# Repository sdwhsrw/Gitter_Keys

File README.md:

# Warning: The project is still in progress.
# The project code and design files have not yet been organized and uploaded.

# Gitter_Keys
Gitter is an open-source key matrix project. Gitter_Keys is the mechanical keys key version of it. 

Gitter is designed to easy build. 
It uses raspberry pi pico as controller, which you can easily get with 4 to 5 Euros
The smd components are easy to solder even for beginner. 

# BOM

# Building guide
to be continue

# Links

https://www.instagram.com/wqnmf2046/

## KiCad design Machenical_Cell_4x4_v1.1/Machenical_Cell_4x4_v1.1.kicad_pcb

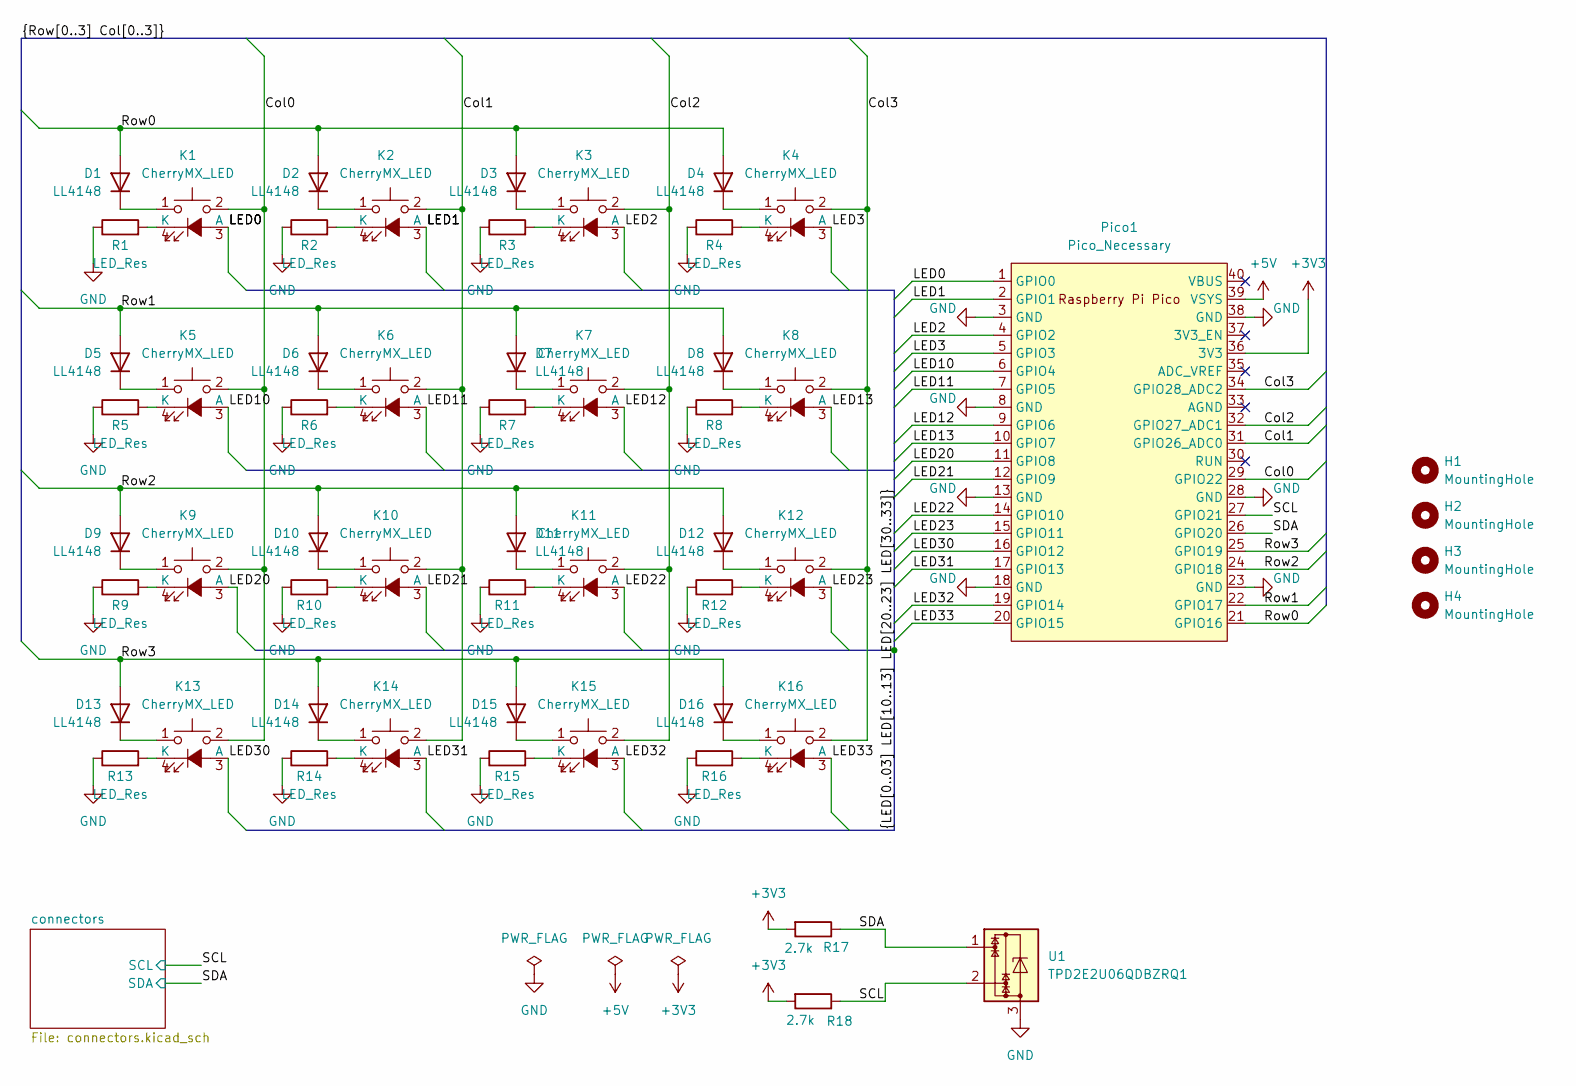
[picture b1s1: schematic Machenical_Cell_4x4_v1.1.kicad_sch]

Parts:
D1, D2, D3, D4, D5, D6, D7, D8, D9, D10, D11, D12, D13, D14, D15, D16: LL4148; D_MiniMELF
H1, H2, H3, H4: MountingHole; Moutinghole_M2.5
K1, K2, K3, K4, K5, K6, K7, K8, K9, K10, K11, K12, K13, K14, K15, K16: CherryMX_LED; MX-Hotswap-1U-1206-Reserved-LED
Pico1: Pico_Necessary; Pico_THR_Necessary
R1, R2, R3, R4, R5, R6, R7, R8, R9, R10, R11, R12, R13, R14, R15, R16: LED_Res; R_0805_2012Metric_Pad1.20x1.40mm_HandSolder
R17, R18: 2.7k; R_0805_2012Metric_Pad1.20x1.40mm_HandSolder
U1: TPD2E2U06QDBZRQ1; SOT-323_SC-70

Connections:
+3V3: Pico1.36 (3V3), R17.2, R18.2; also elsewhere on the board
+5V: Pico1.39 (VSYS); also elsewhere on the board
/Col0: K1.2, K5.2, K9.2, K13.2, Pico1.29 (GPIO22)
/Col1: K2.2, K6.2, K10.2, K14.2, Pico1.31 (GPIO26_ADC0)
/Col2: K3.2, K7.2, K11.2, K15.2, Pico1.32 (GPIO27_ADC1)
/Col3: K4.2, K8.2, K12.2, K16.2, Pico1.34 (GPIO28_ADC2)
/LED0: K1.3 (A), Pico1.1 (GPIO0)
/LED1: K2.3 (A), Pico1.2 (GPIO1)
/LED2: K3.3 (A), Pico1.4 (GPIO2)
/LED3: K4.3 (A), Pico1.5 (GPIO3)
/LED10: K5.3 (A), Pico1.6 (GPIO4)
/LED11: K6.3 (A), Pico1.7 (GPIO5)
/LED12: K7.3 (A), Pico1.9 (GPIO6)
/LED13: K8.3 (A), Pico1.10 (GPIO7)
/LED20: K9.3 (A), Pico1.11 (GPIO8)
/LED21: K10.3 (A), Pico1.12 (GPIO9)
/LED22: K11.3 (A), Pico1.14 (GPIO10)
/LED23: K12.3 (A), Pico1.15 (GPIO11)
/LED30: K13.3 (A), Pico1.16 (GPIO12)
/LED31: K14.3 (A), Pico1.17 (GPIO13)
/LED32: K15.3 (A), Pico1.19 (GPIO14)
/LED33: K16.3 (A), Pico1.20 (GPIO15)
/Row0: D1.2 (A), D2.2 (A), D3.2 (A), D4.2 (A), Pico1.21 (GPIO16)
/Row1: D5.2 (A), D6.2 (A), D7.2 (A), D8.2 (A), Pico1.22 (GPIO17)
/Row2: D9.2 (A), D10.2 (A), D11.2 (A), D12.2 (A), Pico1.24 (GPIO18)
/Row3: D13.2 (A), D14.2 (A), D15.2 (A), D16.2 (A), Pico1.25 (GPIO19)
/SCL: Pico1.27 (GPIO21), R18.1, U1.2; also elsewhere on the board
/SDA: Pico1.26 (GPIO20), R17.1, U1.1; also elsewhere on the board
GND: Pico1.3 (GND), Pico1.8 (GND), Pico1.13 (GND), Pico1.18 (GND), Pico1.23 (GND), Pico1.28 (GND), Pico1.38 (GND), R1.1, R2.1, R3.1, R4.1, R5.1, R6.1, R7.1, R8.1, R9.1, R10.1, R11.1, R12.1, R13.1, R14.1, R15.1, R16.1, U1.3; also elsewhere on the board
unnamed: D1.1 (K), K1.1
unnamed: D2.1 (K), K2.1
unnamed: D3.1 (K), K3.1
unnamed: D4.1 (K), K4.1
unnamed: D5.1 (K), K5.1
unnamed: D6.1 (K), K6.1
unnamed: D7.1 (K), K7.1
unnamed: D8.1 (K), K8.1
unnamed: D9.1 (K), K9.1
unnamed: D10.1 (K), K10.1
unnamed: D11.1 (K), K11.1
unnamed: D12.1 (K), K12.1
unnamed: D13.1 (K), K13.1
unnamed: D14.1 (K), K14.1
unnamed: D15.1 (K), K15.1
unnamed: D16.1 (K), K16.1
unnamed: K1.4 (K), R1.2
unnamed: K2.4 (K), R2.2
unnamed: K3.4 (K), R3.2
unnamed: K4.4 (K), R4.2
unnamed: K5.4 (K), R5.2
unnamed: K6.4 (K), R6.2
unnamed: K7.4 (K), R7.2
unnamed: K8.4 (K), R8.2
unnamed: K9.4 (K), R9.2
unnamed: K10.4 (K), R10.2
unnamed: K11.4 (K), R11.2
unnamed: K12.4 (K), R12.2
unnamed: K13.4 (K), R13.2
unnamed: K14.4 (K), R14.2
unnamed: K15.4 (K), R15.2
unnamed: K16.4 (K), R16.2

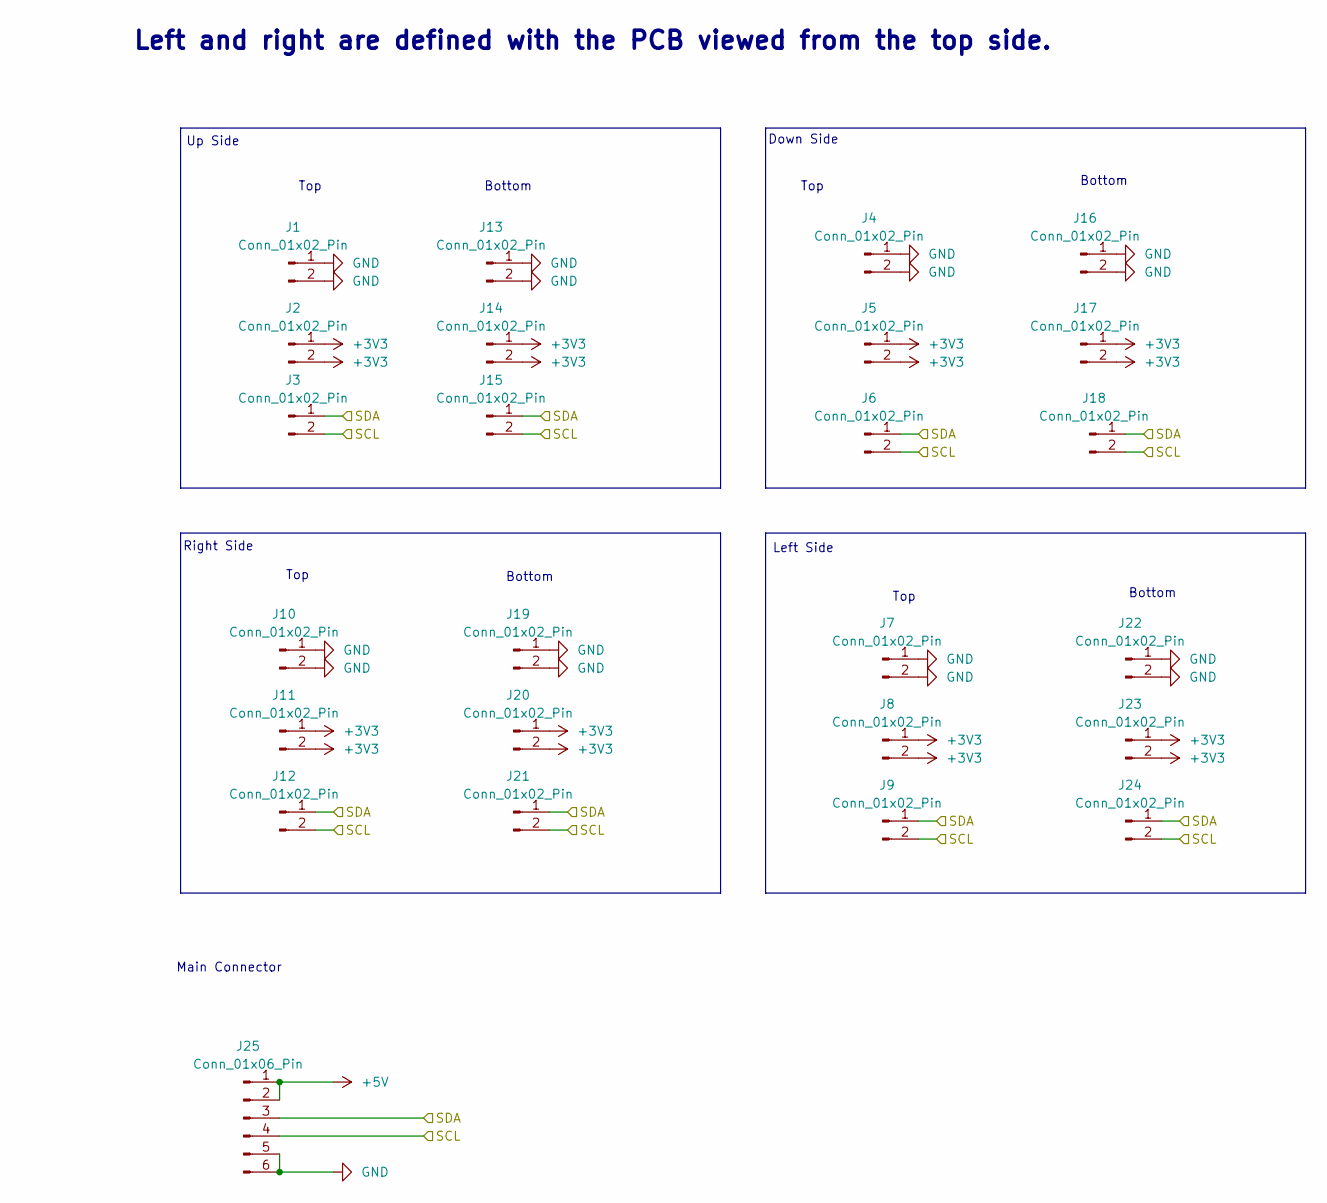
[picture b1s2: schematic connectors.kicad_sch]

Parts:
J1, J2, J3, J4, J5, J6, J7, J8, J9, J10, J11, J12, J13, J14, J15, J16, J17, J18, J19, J20, J21, J22, J23, J24: Conn_01x02_Pin; SolderPad_2
J25: Conn_01x06_Pin; PinHeader_1x06_P2.54mm_Vertical

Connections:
+3V3: J2.1, J2.2, J5.1, J5.2, J8.1, J8.2, J11.1, J11.2, J14.1, J14.2, J17.1, J17.2, J20.1, J20.2, J23.1, J23.2; also elsewhere on the board
+5V: J25.1, J25.2; also elsewhere on the board
/SCL: J3.2, J6.2, J9.2, J12.2, J15.2, J18.2, J21.2, J24.2, J25.4; also elsewhere on the board
/SDA: J3.1, J6.1, J9.1, J12.1, J15.1, J18.1, J21.1, J24.1, J25.3; also elsewhere on the board
GND: J1.1, J1.2, J4.1, J4.2, J7.1, J7.2, J10.1, J10.2, J13.1, J13.2, J16.1, J16.2, J19.1, J19.2, J22.1, J22.2, J25.5, J25.6; also elsewhere on the board

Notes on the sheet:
Bottom
Up Side
Top
Left Side
Down Side
Right Side
Left and right are defined with the PCB viewed from the top side.
Main Connector

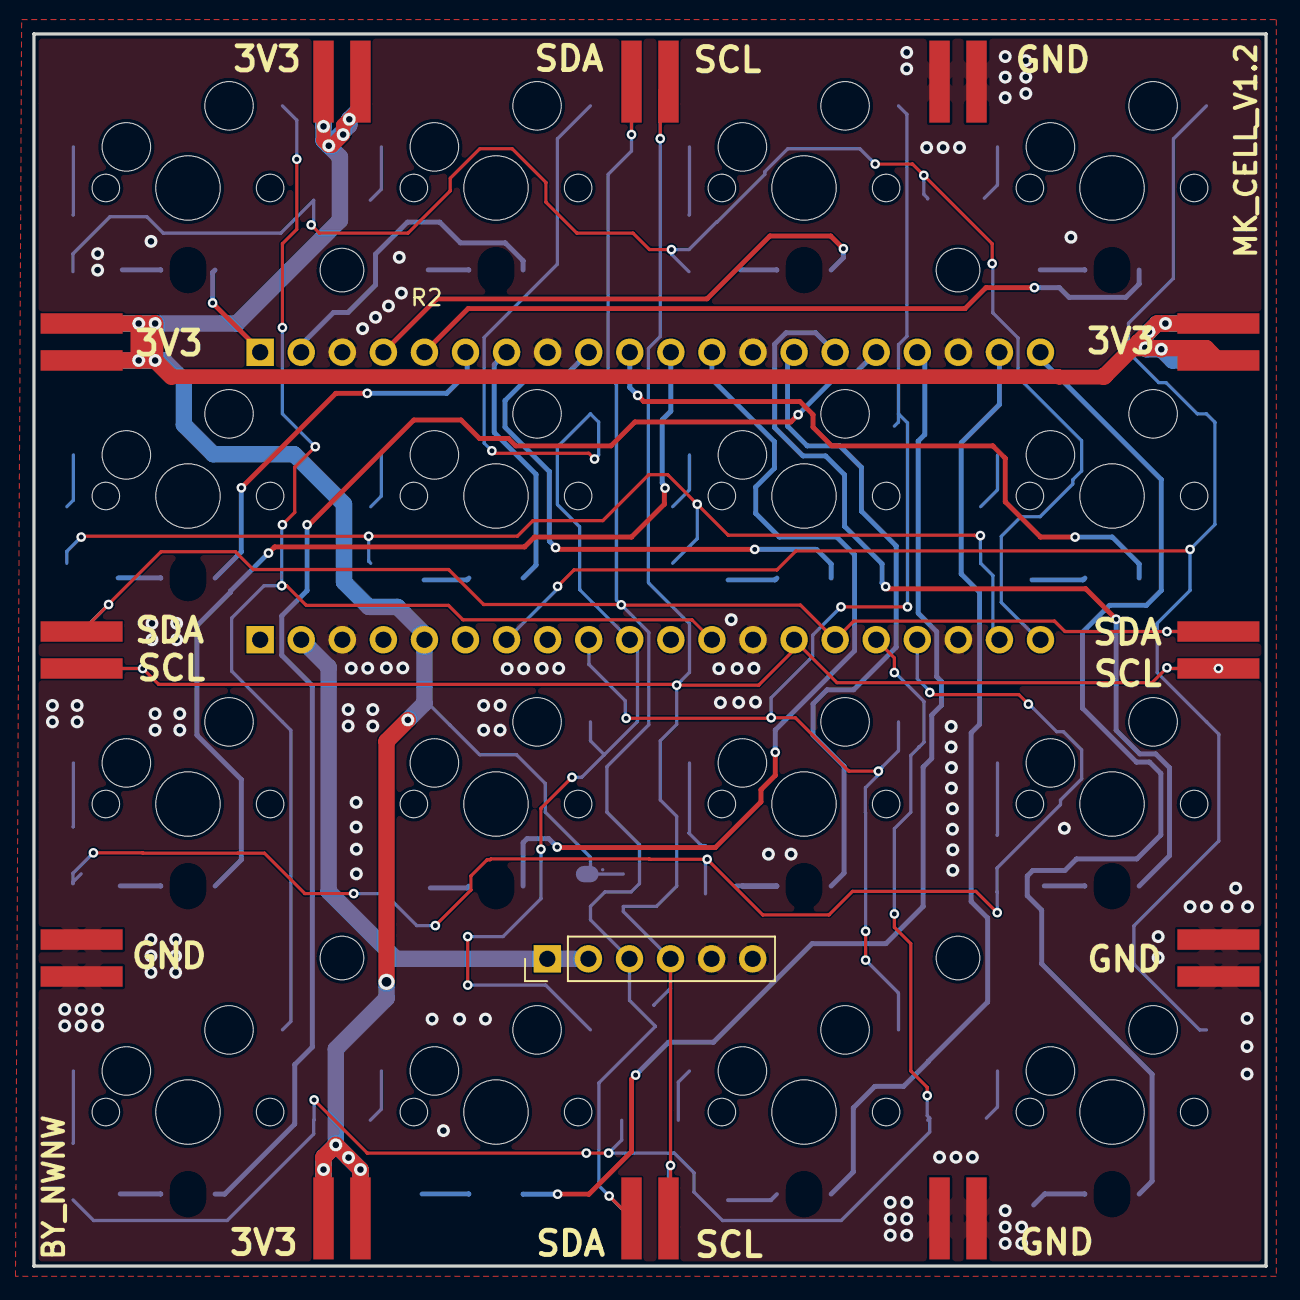
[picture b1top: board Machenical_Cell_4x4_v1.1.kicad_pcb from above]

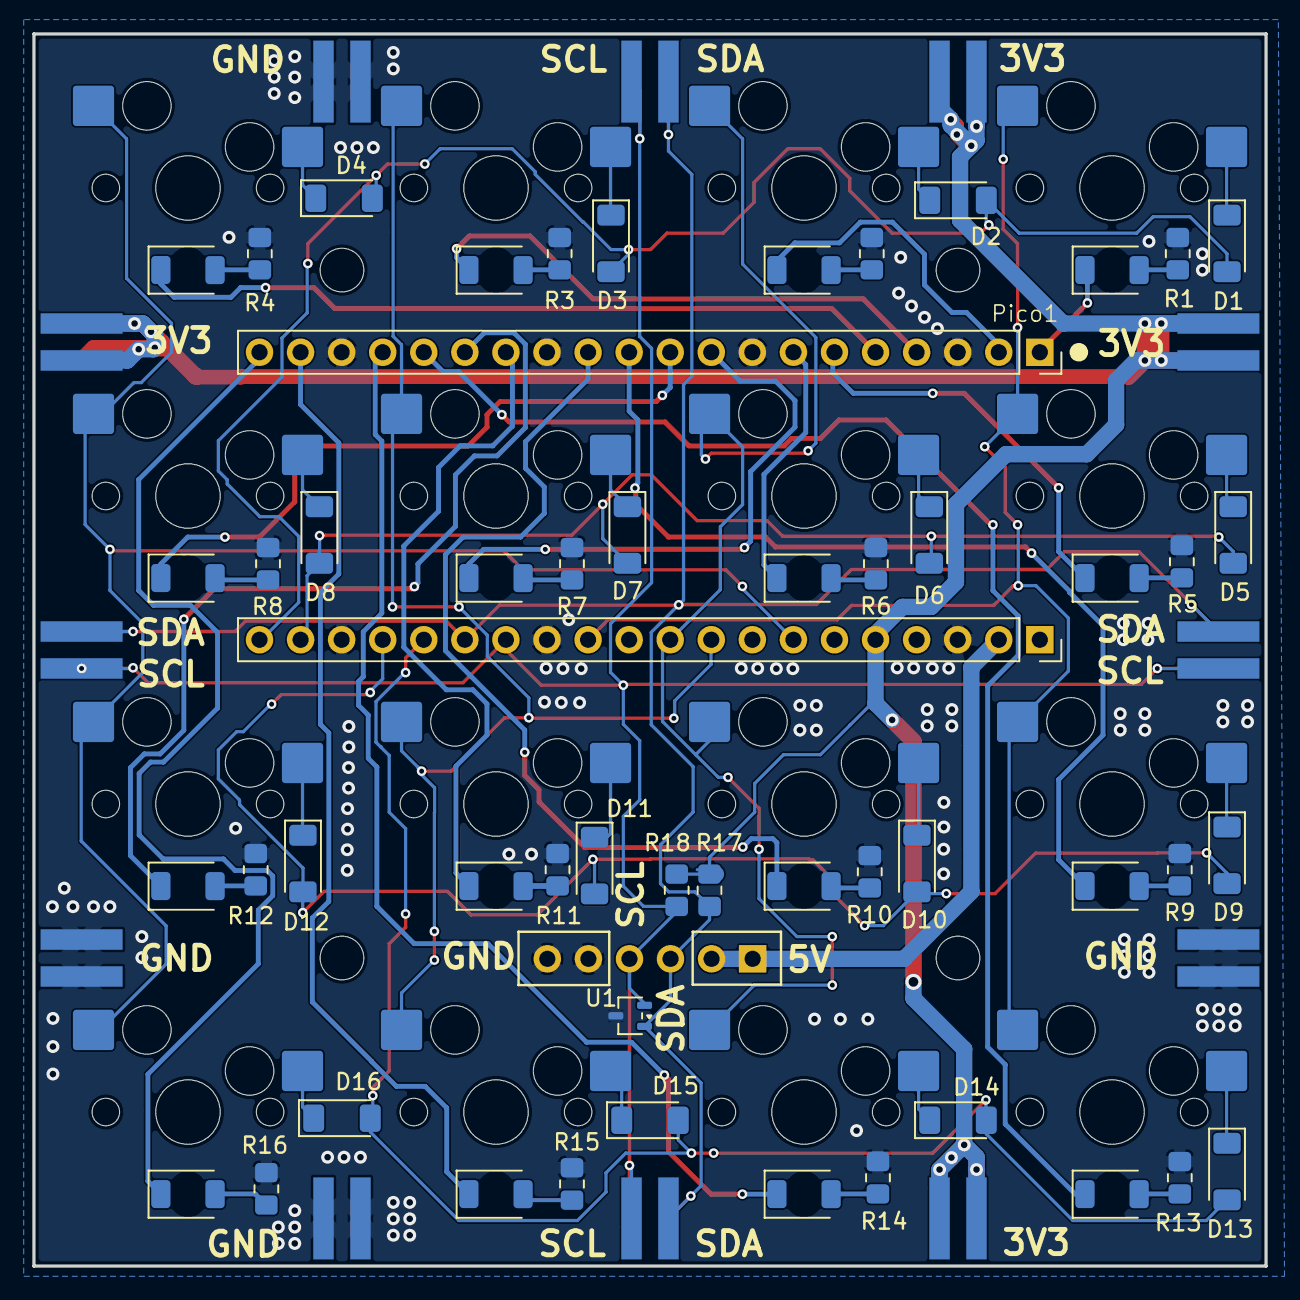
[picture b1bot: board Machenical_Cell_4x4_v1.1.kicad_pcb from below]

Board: 2 copper layers, 76.2 x 76.2 mm, 81 parts (48 on the bottom side), 61 nets.

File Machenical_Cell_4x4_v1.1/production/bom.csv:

Designator,Footprint,Quantity,Value,LCSC Part #
"D1, D10, D11, D12, D13, D14, D15, D16, D2, D3, D4, D5, D6, D7, D8, D9",D_MiniMELF,16,LL4148,
"H1, H2, H3, H4",Moutinghole_M2.5,4,MountingHole,
"J1, J10, J11, J12, J13, J14, J15, J16, J17, J18, J19, J2, J20, J21, J22, J23, J24, J3, J4, J5, J6, J7, J8, J9",SolderPad_2,24,Conn_01x02_Pin,
J25,PinHeader_1x06_P2.54mm_Vertical,1,Conn_01x06_Pin,
"K1, K10, K11, K12, K13, K14, K15, K16, K2, K3, K4, K5, K6, K7, K8, K9",MX-Hotswap-1U-1206-Reserved-LED,16,CherryMX_LED,
PICO1,Pico_THR_Necessary,1,Pico_Necessary,
"R1, R10, R11, R12, R13, R14, R15, R16, R2, R3, R4, R5, R6, R7, R8, R9",0805,16,LED_Res,
"R17, R18",0805,2,2.7k,
U1,SOT-323_SC-70,1,TPD2E2U06QDBZRQ1,

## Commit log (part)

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2026-05-23 change folder name
2026-05-23 improve code
2026-05-23 improve i2c robustness
2026-05-24 setup raw tinyusb, fix configuration descriptor endpoint mapping
2026-05-24 gitignore
2026-05-24 Firmware Version V1.2
    setup raw tinyusb, fix configuration descriptor endpoint mapping
    improve i2c robustness
    improve code format
2026-06-15 add necessary setup
2026-06-15 git ignore kicad backup folder
2026-06-15 update to KICAD 10
